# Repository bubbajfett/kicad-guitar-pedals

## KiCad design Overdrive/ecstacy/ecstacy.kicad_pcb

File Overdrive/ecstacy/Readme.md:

# Ecstacy

This is a clone of the Wampler ecstacy  overdrive.  

So this pedal is verified. I have not boxed this one yet, either.

All trademarks belong to their respective owners.

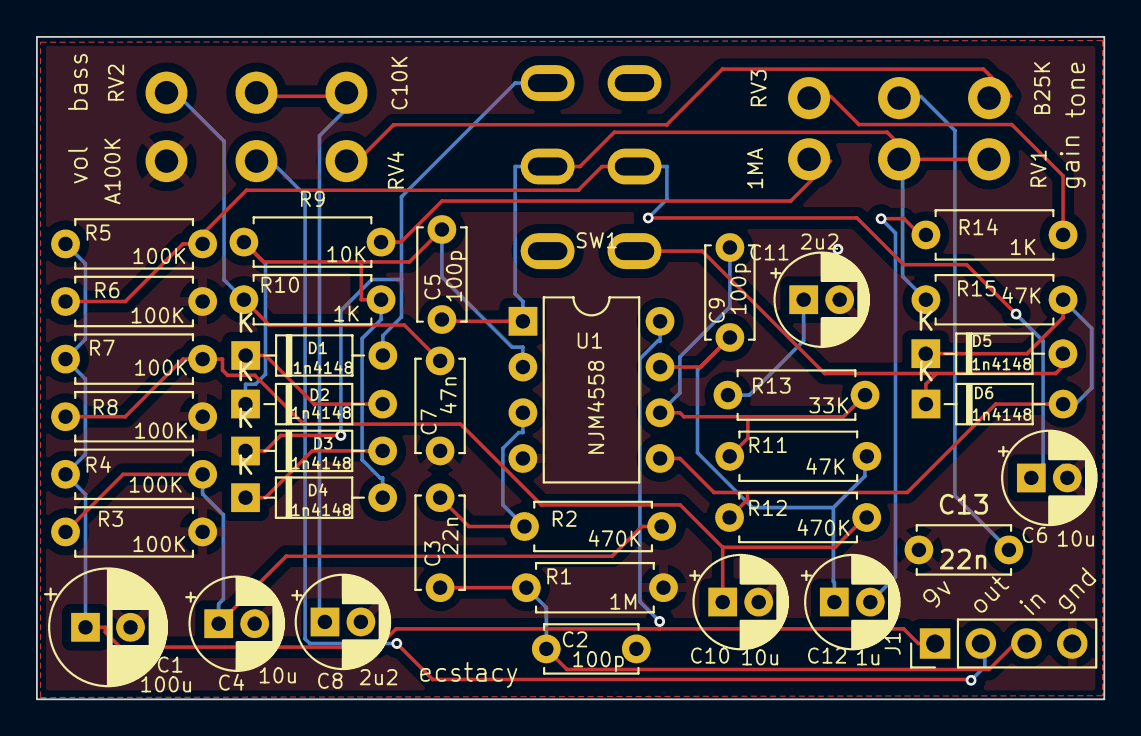
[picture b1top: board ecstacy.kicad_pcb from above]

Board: 2 copper layers, 59.3 x 36.8 mm, 41 parts (0 on the bottom side), 25 nets.

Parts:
C1: 100u; CP_Radial_D6.3mm_P2.50mm
C2, C5, C9: 100p; C_Disc_D5.0mm_W2.5mm_P5.00mm
C3, C13: 22n; C_Disc_D5.0mm_W2.5mm_P5.00mm
C4, C6, C10: 10u; CP_Radial_D5.0mm_P2.00mm
C7: 47n; C_Disc_D5.0mm_W2.5mm_P5.00mm
C8, C11: 2u2; CP_Radial_D5.0mm_P2.00mm
C12: 1u; CP_Radial_D5.0mm_P2.00mm
D1, D2, D3, D4, D5, D6: 1n4148; D_DO-35_SOD27_P7.62mm_Horizontal
J1: Conn_01x04_Pin; PinHeader_1x04_P2.54mm_Vertical
R1: 1M; R_Axial_DIN0207_L6.3mm_D2.5mm_P7.62mm_Horizontal
R2, R12: 470K; R_Axial_DIN0207_L6.3mm_D2.5mm_P7.62mm_Horizontal
R3, R4, R5, R6, R7, R8: 100K; R_Axial_DIN0207_L6.3mm_D2.5mm_P7.62mm_Horizontal
R9: 10K; R_Axial_DIN0207_L6.3mm_D2.5mm_P7.62mm_Horizontal
R10, R14: 1K; R_Axial_DIN0207_L6.3mm_D2.5mm_P7.62mm_Horizontal
R11, R15: 47K; R_Axial_DIN0207_L6.3mm_D2.5mm_P7.62mm_Horizontal
R13: 33K; R_Axial_DIN0207_L6.3mm_D2.5mm_P7.62mm_Horizontal
RV1: 1MA; Pot_Underside
RV2: C10K; Pot_Underside
RV3: B25K; Pot_Underside
RV4: A100K; Pot_Underside
SW1: SW_DPDT_x2; SWITCH-M1-DPDT
U1: NJM4558; DIP-8_W7.62mm

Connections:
9v: C1.1, J1.1, R4.1, R5.1, R7.1, U1.8 (V+)
GND: C1.2, C2.2, C4.2, C6.2, C7.1, C8.2, C10.2, C11.2, C13.1, J1.4, R1.2, R3.2, R6.2, R8.2, RV4.1, U1.4 (V-)
unnamed: C7.2, R10.1, RV2.3
unnamed: C8.1, RV2.1, RV2.2
unnamed: C11.1, R13.1
unnamed: C9.1, C12.1, R11.2, U1.7
unnamed: C12.2, R14.1
unnamed: C13.2, RV3.2
unnamed: D1.2 (A), D3.1 (K), SW1.1 (A)
unnamed: D1.1 (K), D2.2 (A)
unnamed: C5.2, D2.1 (K), D4.2 (A), R9.1, R10.2, U1.2 (-)
unnamed: D3.2 (A), D4.1 (K)
unnamed: D5.2 (A), D6.1 (K), SW1.6 (C)
unnamed: D5.1 (K), D6.2 (A), R12.1, R15.2, U1.5 (+)
unnamed: R9.2, RV1.1
unnamed: R14.2, RV3.3
unnamed: RV3.1, RV4.3
unnamed: C5.1, R15.1, RV1.2, RV1.3, SW1.2 (B), U1.1
unnamed: C3.2, R2.1, U1.3 (+)
unnamed: C9.2, R11.1, R13.2, U1.6 (-)
VB1: C4.1, R2.2, R3.1, R4.2
VB2: C6.1, R5.2, R6.1, SW1.5 (B)
VB3: C10.1, R7.2, R8.1, R12.2
in: C2.1, C3.1, J1.3, R1.1
out: J1.2, RV4.2

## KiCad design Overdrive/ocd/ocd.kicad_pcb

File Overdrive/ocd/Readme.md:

# ocd

This is a clone of the Fulltone OCD overdrive.

This pedal is verified. I have not boxed this one yet.

All trademarks belong to their respective owners.

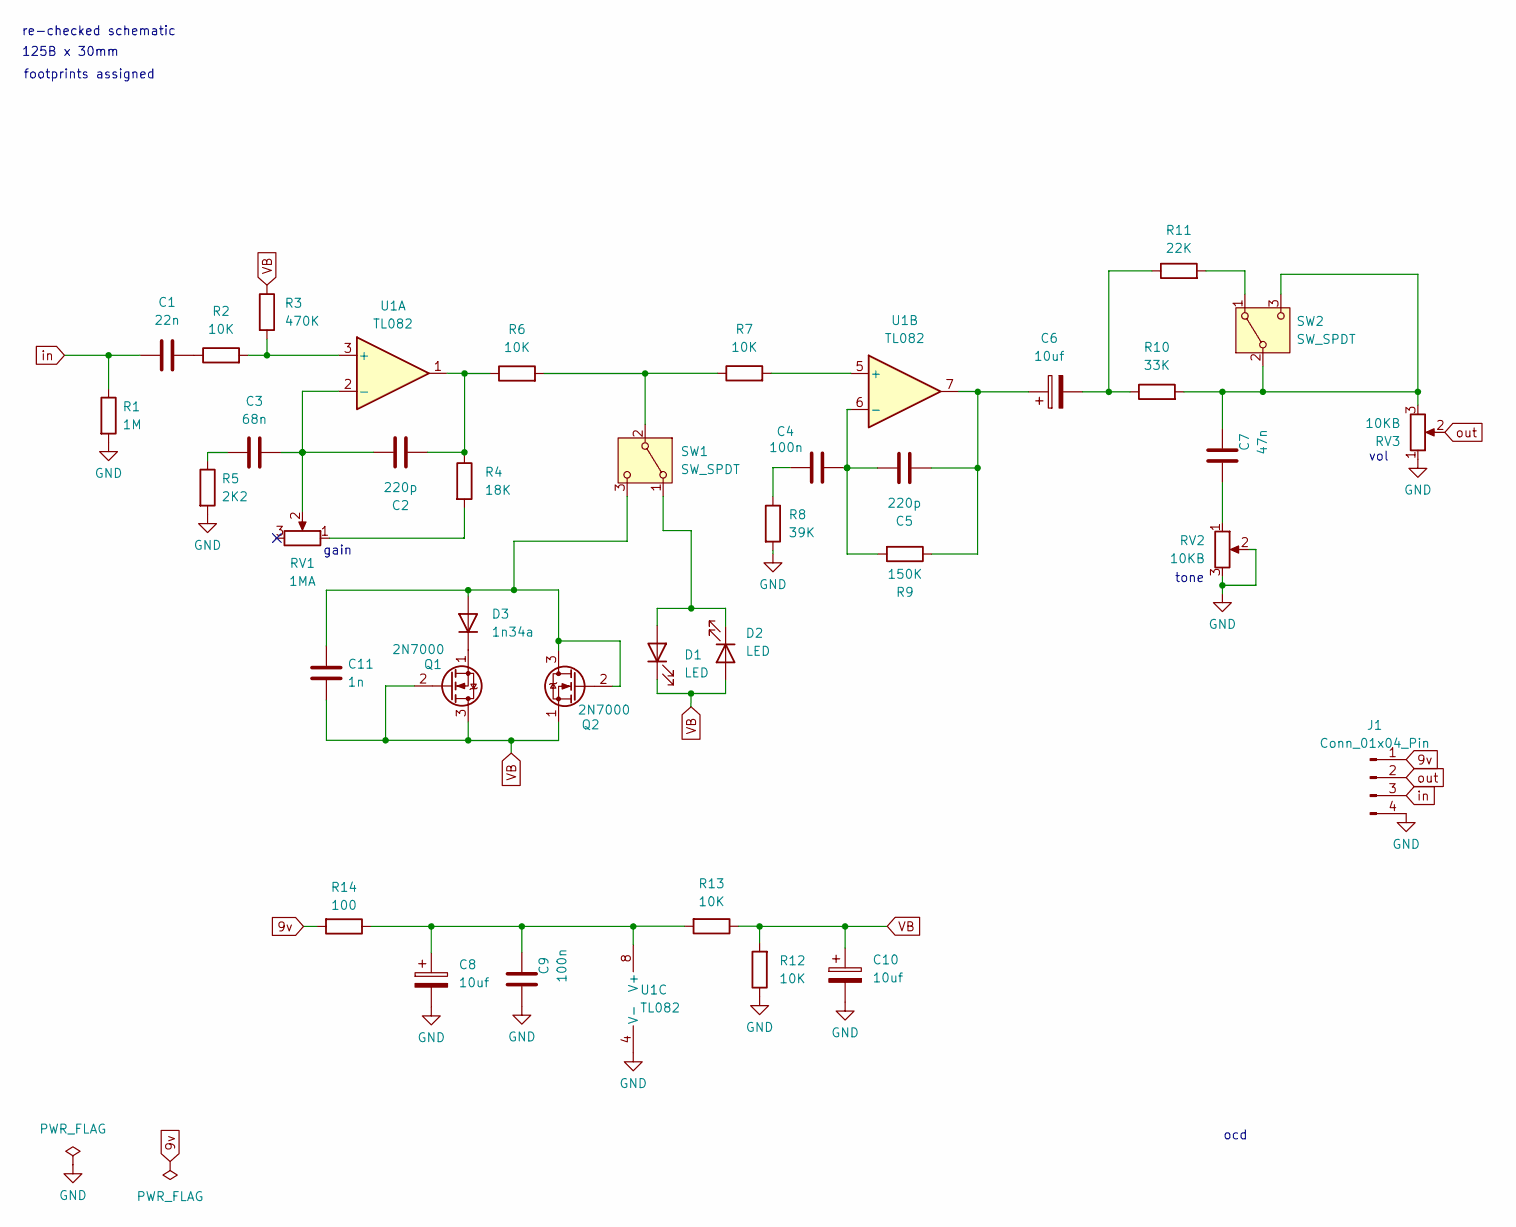
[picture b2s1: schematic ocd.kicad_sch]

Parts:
C1: 22n; C_Rect_L7.0mm_W2.0mm_P5.00mm
C2, C5: 220p; C_Rect_L7.0mm_W2.0mm_P5.00mm
C3: 68n; C_Rect_L7.0mm_W2.0mm_P5.00mm
C4, C9: 100n; C_Rect_L7.0mm_W2.0mm_P5.00mm
C6, C8, C10: 10uf; CP_Radial_D5.0mm_P2.00mm
C7: 47n; C_Rect_L7.0mm_W2.0mm_P5.00mm
C11: 1n; C_Rect_L7.0mm_W2.0mm_P5.00mm
D1, D2: LED; LED_D3.0mm
D3: 1n34a; D_DO-34_SOD68_P7.62mm_Horizontal
J1: Conn_01x04_Pin; PinHeader_1x04_P2.54mm_Vertical
Q1, Q2: 2N7000; TO-92_Inline
R1: 1M; R_Axial_DIN0207_L6.3mm_D2.5mm_P7.62mm_Horizontal
R2, R6, R7, R12, R13: 10K; R_Axial_DIN0207_L6.3mm_D2.5mm_P7.62mm_Horizontal
R3: 470K; R_Axial_DIN0207_L6.3mm_D2.5mm_P7.62mm_Horizontal
R4: 18K; R_Axial_DIN0207_L6.3mm_D2.5mm_P7.62mm_Horizontal
R5: 2K2; R_Axial_DIN0207_L6.3mm_D2.5mm_P7.62mm_Horizontal
R8: 39K; R_Axial_DIN0207_L6.3mm_D2.5mm_P7.62mm_Horizontal
R9: 150K; R_Axial_DIN0207_L6.3mm_D2.5mm_P7.62mm_Horizontal
R10: 33K; R_Axial_DIN0207_L6.3mm_D2.5mm_P7.62mm_Horizontal
R11: 22K; R_Axial_DIN0207_L6.3mm_D2.5mm_P7.62mm_Horizontal
R14: 100; R_Axial_DIN0207_L6.3mm_D2.5mm_P7.62mm_Horizontal
RV1: 1MA; Pot_Underside
RV2, RV3: 10KB; Pot_Underside
SW1, SW2: SW_SPDT; SWITCH-M1-SPDT
U1: TL082; DIP-8_W7.62mm

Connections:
9v: J1.1, R14.2
GND: C8.2, C9.1, C10.2, J1.4, R1.2, R5.2, R8.2, R12.1, RV2.2, RV2.3, RV3.1, U1.4 (V-)
unnamed: C1.2, R2.1
unnamed: C2.1, R4.1, R6.1, U1.1
unnamed: C3.1, R5.1
unnamed: C4.1, R8.1
unnamed: C5.1, C6.1, R9.1, U1.7
unnamed: C6.2, R10.1, R11.1
unnamed: C7.1, RV2.1
unnamed: D1.2 (A), D2.1 (K), SW1.1 (A)
unnamed: C11.2, D3.2 (A), Q2.2 (G), Q2.3 (D), SW1.3 (C)
unnamed: D3.1 (K), Q1.1 (S)
unnamed: R4.2, RV1.1
unnamed: R6.2, R7.1, SW1.2 (B)
unnamed: R11.2, SW2.1 (A)
unnamed: C7.2, R10.2, RV3.3, SW2.2 (B), SW2.3 (C)
unnamed: R2.2, R3.2, U1.3 (+)
unnamed: C2.2, C3.2, RV1.2, U1.2 (-)
unnamed: R7.2, U1.5 (+)
unnamed: C4.2, C5.2, R9.2, U1.6 (-)
unnamed: C8.1, C9.2, R13.2, R14.1, U1.8 (V+)
VB: C10.1, C11.1, D1.1 (K), D2.2 (A), Q1.2 (G), Q1.3 (D), Q2.1 (S), R3.1, R12.2, R13.1
in: C1.1, J1.3, R1.1
out: J1.2, RV3.2

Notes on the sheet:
footprints assigned
vol
tone
125B x 30mm
gain
re-checked schematic
ocd

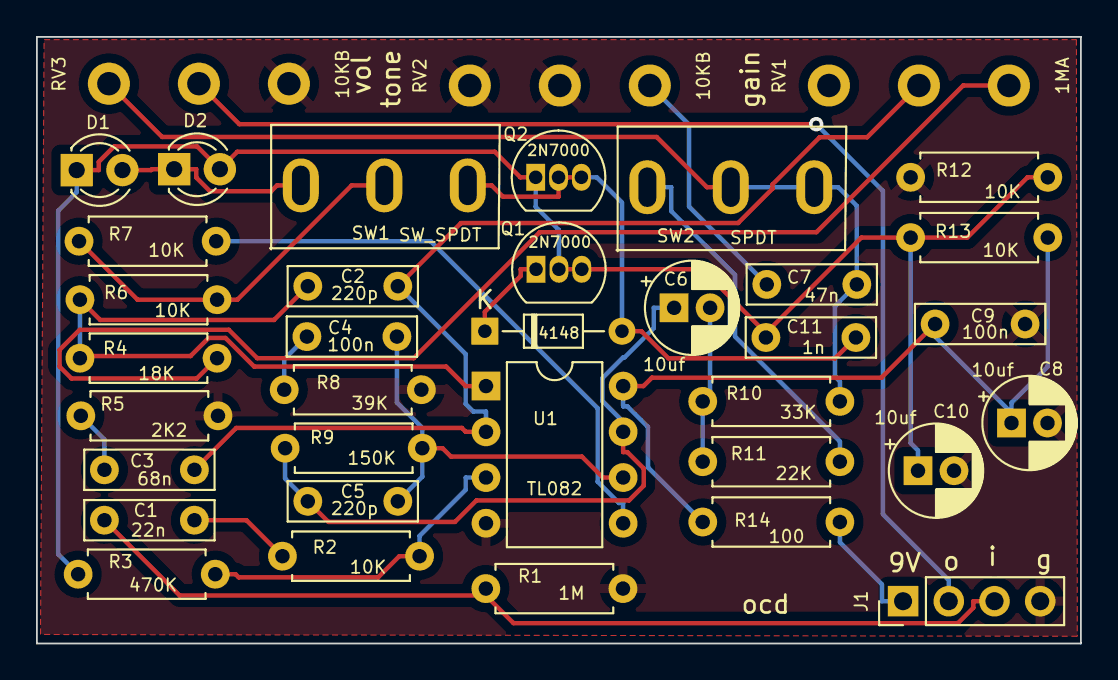
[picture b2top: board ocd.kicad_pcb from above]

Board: 2 copper layers, 58.0 x 33.7 mm, 37 parts (0 on the bottom side), 24 nets.

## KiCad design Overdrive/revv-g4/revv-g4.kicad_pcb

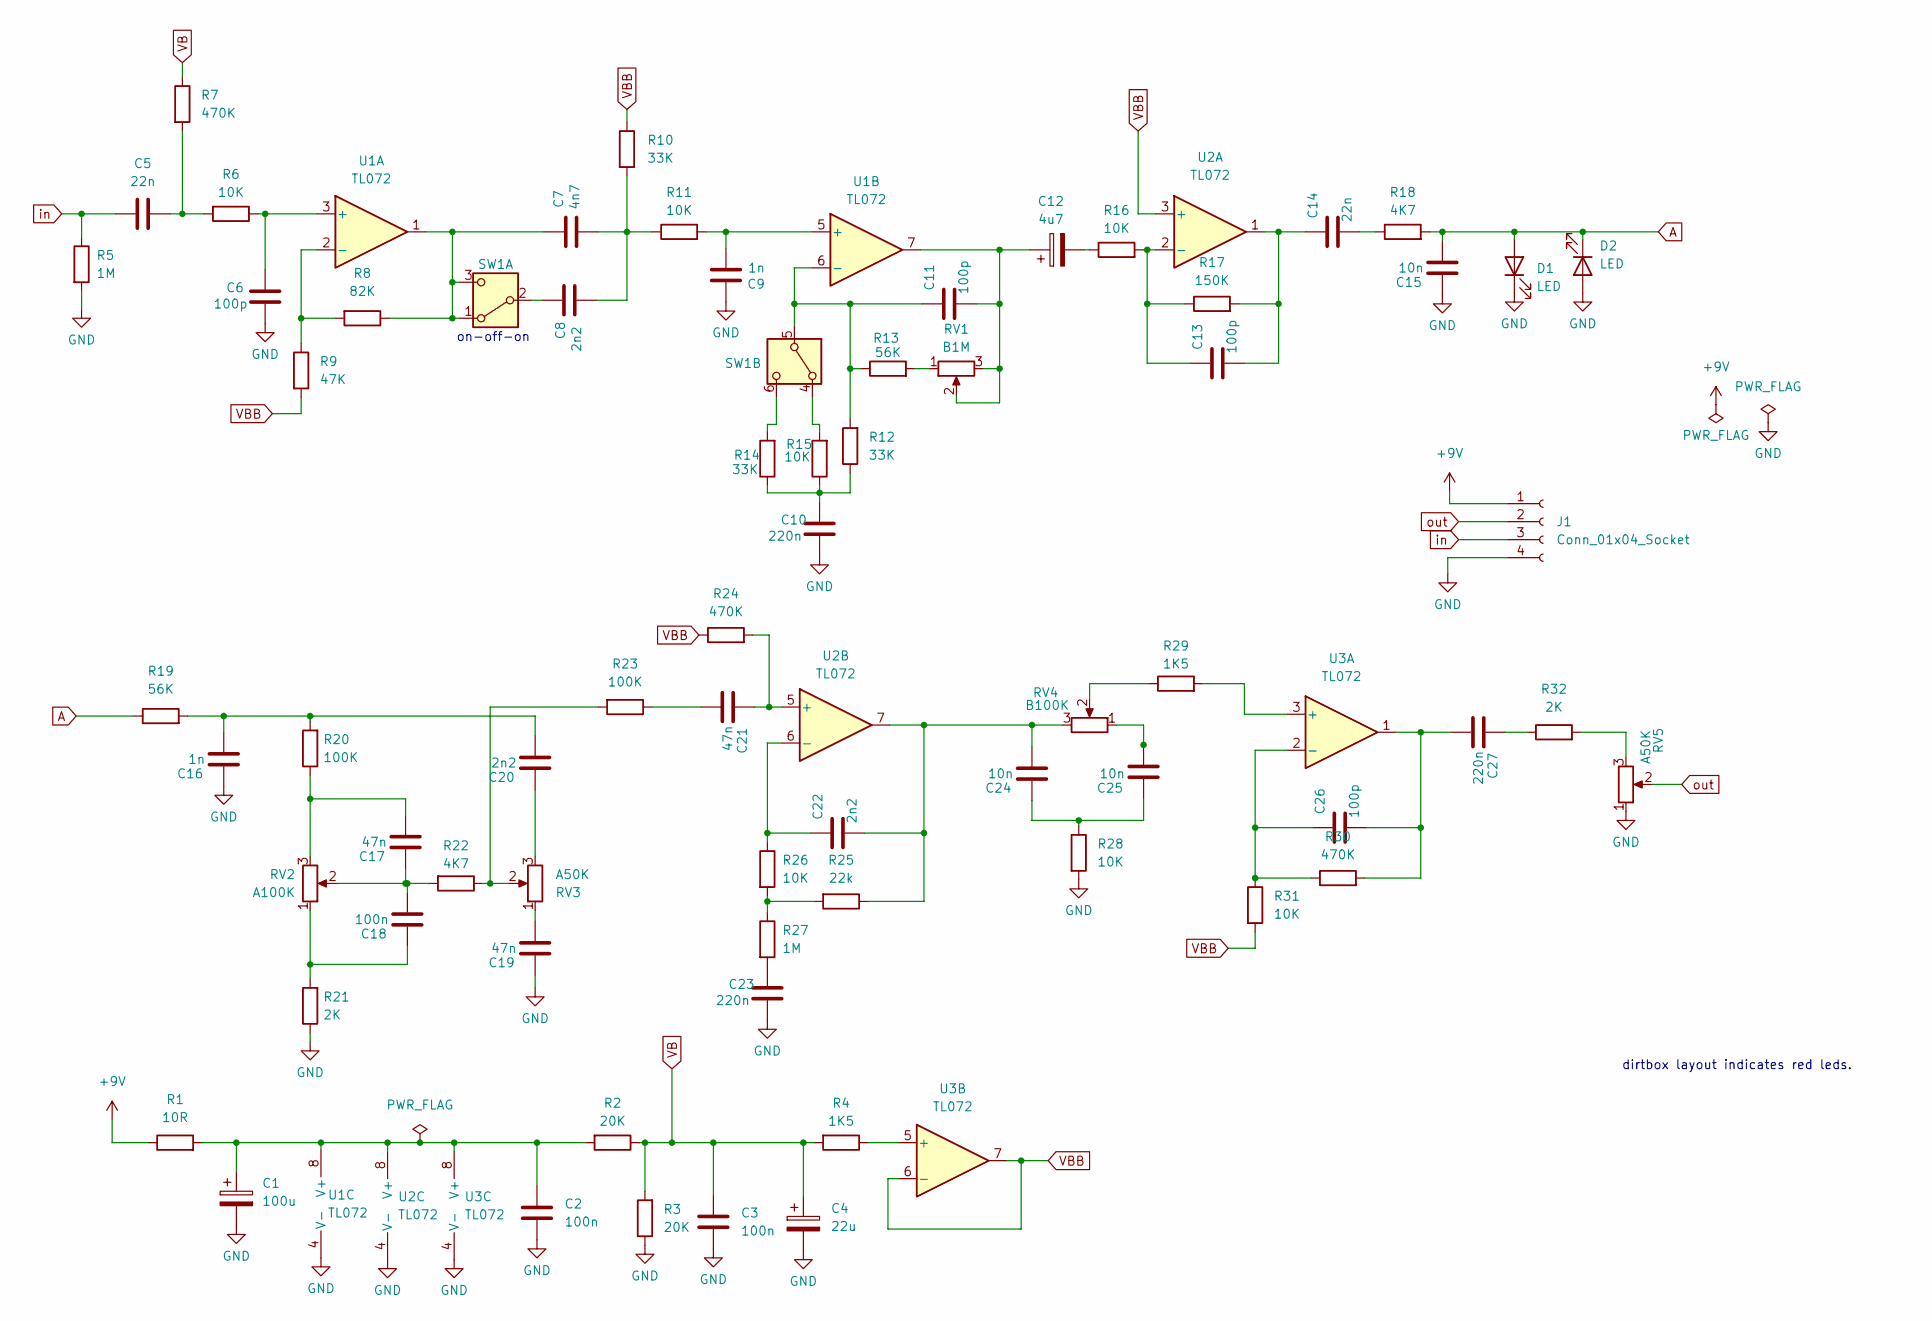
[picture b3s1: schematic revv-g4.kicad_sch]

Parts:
C1: 100u; CP_Radial_D6.3mm_P2.50mm
C2, C3, C18: 100n; C_Rect_L7.0mm_W3.5mm_P5.00mm
C4: 22u; CP_Radial_D5.0mm_P2.00mm
C5, C14: 22n; C_Rect_L7.0mm_W3.5mm_P5.00mm
C6, C11, C13, C26: 100p; C_Disc_D4.7mm_W2.5mm_P5.00mm
C7: 4n7; C_Rect_L7.0mm_W3.5mm_P5.00mm
C8, C20, C22: 2n2; C_Rect_L7.0mm_W3.5mm_P5.00mm
C9, C16: 1n; C_Rect_L7.0mm_W3.5mm_P5.00mm
C10, C23, C27: 220n; C_Rect_L7.0mm_W3.5mm_P5.00mm
C12: 4u7; CP_Radial_D5.0mm_P2.00mm
C15, C24, C25: 10n; C_Rect_L7.0mm_W3.5mm_P5.00mm
C17, C19, C21: 47n; C_Rect_L7.0mm_W3.5mm_P5.00mm
D1, D2: LED; LED_D3.0mm
J1: Conn_01x04_Socket; PinHeader_1x04_P2.54mm_Vertical
R1: 10R; R_Axial_DIN0207_L6.3mm_D2.5mm_P7.62mm_Horizontal
R2, R3: 20K; R_Axial_DIN0207_L6.3mm_D2.5mm_P7.62mm_Horizontal
R4, R29: 1K5; R_Axial_DIN0207_L6.3mm_D2.5mm_P7.62mm_Horizontal
R5, R27: 1M; R_Axial_DIN0207_L6.3mm_D2.5mm_P7.62mm_Horizontal
R6, R11, R15, R16, R26, R28, R31: 10K; R_Axial_DIN0207_L6.3mm_D2.5mm_P7.62mm_Horizontal
R7, R24, R30: 470K; R_Axial_DIN0207_L6.3mm_D2.5mm_P7.62mm_Horizontal
R8: 82K; R_Axial_DIN0207_L6.3mm_D2.5mm_P7.62mm_Horizontal
R9: 47K; R_Axial_DIN0207_L6.3mm_D2.5mm_P7.62mm_Horizontal
R10, R12, R14: 33K; R_Axial_DIN0207_L6.3mm_D2.5mm_P7.62mm_Horizontal
R13, R19: 56K; R_Axial_DIN0207_L6.3mm_D2.5mm_P7.62mm_Horizontal
R17: 150K; R_Axial_DIN0207_L6.3mm_D2.5mm_P7.62mm_Horizontal
R18, R22: 4K7; R_Axial_DIN0207_L6.3mm_D2.5mm_P7.62mm_Horizontal
R20, R23: 100K; R_Axial_DIN0207_L6.3mm_D2.5mm_P7.62mm_Horizontal
R21, R32: 2K; R_Axial_DIN0207_L6.3mm_D2.5mm_P7.62mm_Horizontal
R25: 22k; R_Axial_DIN0207_L6.3mm_D2.5mm_P7.62mm_Horizontal
RV1: B1M; Pot_Underside
RV2: A100K; Pot_Underside
RV3, RV5: A50K; Pot_Underside
RV4: B100K; Pot_Underside
SW1: SW_DPDT_x2; SWITCH-M1-DPDT
U1, U2, U3: TL072; DIP-8_W7.62mm

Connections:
+9V: J1.1, R1.1
A: C15.1, D1.2 (A), D2.1 (K), R18.2, R19.1
GND: C1.2, C2.2, C3.2, C4.2, C6.1, C9.2, C10.1, C15.2, C16.2, C19.2, C23.1, D1.1 (K), D2.2 (A), J1.4, R3.1, R5.2, R21.1, R28.2, RV5.1, U1.4 (V-), U2.4 (V-), U3.4 (V-)
unnamed: C5.2, R6.2, R7.2
unnamed: C7.1, C8.1, R10.2, R11.1
unnamed: C10.2, R12.1, R14.1, R15.1
unnamed: C11.1, C12.1, RV1.2, RV1.3, U1.7
unnamed: C12.2, R16.1
unnamed: C13.1, C14.2, R17.2, U2.1
unnamed: C14.1, R18.1
unnamed: C16.1, C20.1, R19.2, R20.2
unnamed: C17.1, R20.1, RV2.3
unnamed: C17.2, C18.1, R22.2, RV2.2
unnamed: C18.2, R21.2, RV2.1
unnamed: C19.1, RV3.1
unnamed: C20.2, RV3.3
unnamed: C21.1, R23.1
unnamed: C22.1, C24.1, R25.1, RV4.3, U2.7
unnamed: C23.2, R27.2
unnamed: C24.2, C25.2, R28.1
unnamed: C25.1, RV4.1
unnamed: C26.1, C27.1, R30.2, U3.1
unnamed: C27.2, R32.1
unnamed: R13.2, RV1.1
unnamed: R22.1, R23.2, RV3.2
unnamed: R25.2, R26.2, R27.1
unnamed: R29.1, RV4.2
unnamed: R32.2, RV5.3
unnamed: C7.2, R8.1, SW1.1 (A), SW1.3 (C), U1.1
unnamed: C8.2, SW1.2 (B)
unnamed: R15.2, SW1.4 (A)
unnamed: C11.2, R12.2, R13.1, SW1.5 (B), U1.6 (-)
unnamed: R14.2, SW1.6 (C)
unnamed: C6.2, R6.1, U1.3 (+)
unnamed: R8.2, R9.1, U1.2 (-)
unnamed: C9.1, R11.2, U1.5 (+)
unnamed: C1.1, C2.1, R1.2, R2.2, U1.8 (V+), U2.8 (V+), U3.8 (V+)
unnamed: C13.2, R16.2, R17.1, U2.2 (-)
unnamed: C21.2, R24.2, U2.5 (+)
unnamed: C22.2, R26.1, U2.6 (-)
unnamed: R29.2, U3.3 (+)
unnamed: C26.2, R30.1, R31.1, U3.2 (-)
unnamed: R4.1, U3.5 (+)
VB: C3.1, C4.1, R2.1, R3.2, R4.2, R7.1
VBB: R9.2, R10.1, R24.1, R31.2, U2.3 (+), U3.6 (-), U3.7
in: C5.1, J1.3, R5.1
out: J1.2, RV5.2

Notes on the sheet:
dirtbox layout indicates red leds.
on-off-on

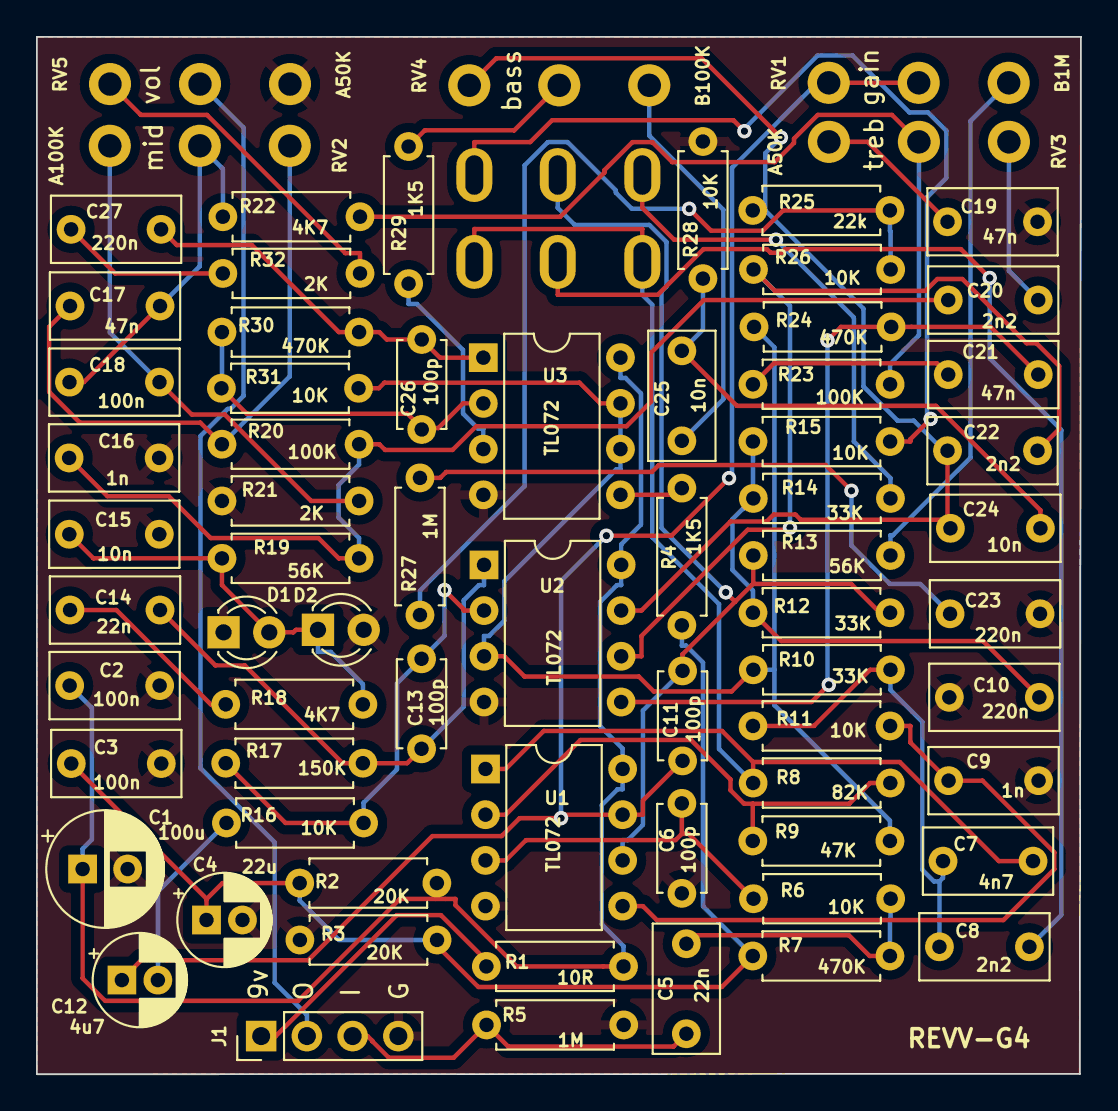
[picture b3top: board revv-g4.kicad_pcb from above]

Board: 2 copper layers, 58.0 x 57.6 mm, 71 parts (0 on the bottom side), 47 nets.

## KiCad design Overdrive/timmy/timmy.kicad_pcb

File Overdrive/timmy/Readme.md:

# Timmy clone

This is a clone of the Paul Cochrane Timmy overdrive.

This pedal is verified, though the layout is poor, IMHO.

It is the first pedal I did in Kicad, and it took 4 revisions
to get a working pedal, going all the way back to 2022.   This was
in the hall of shame box for some time.

v1:  pads for switch too small.   Changed to 2.5mm hole

v2:  RV2 is backwards from the tagboardeffects layout.   I.e.
the schematic has multiple issues.

Pedal has low volume.   Managed to get this to work correctly
via a series of bodges.  Also note te 3.3K resistor R2 is
diff in tagboardeffects layout 

v3:  Seems to work correctly.    Missing some values on
the silkscreen layer.

v4:  final version.      

All trademarks belong to their respective owners.

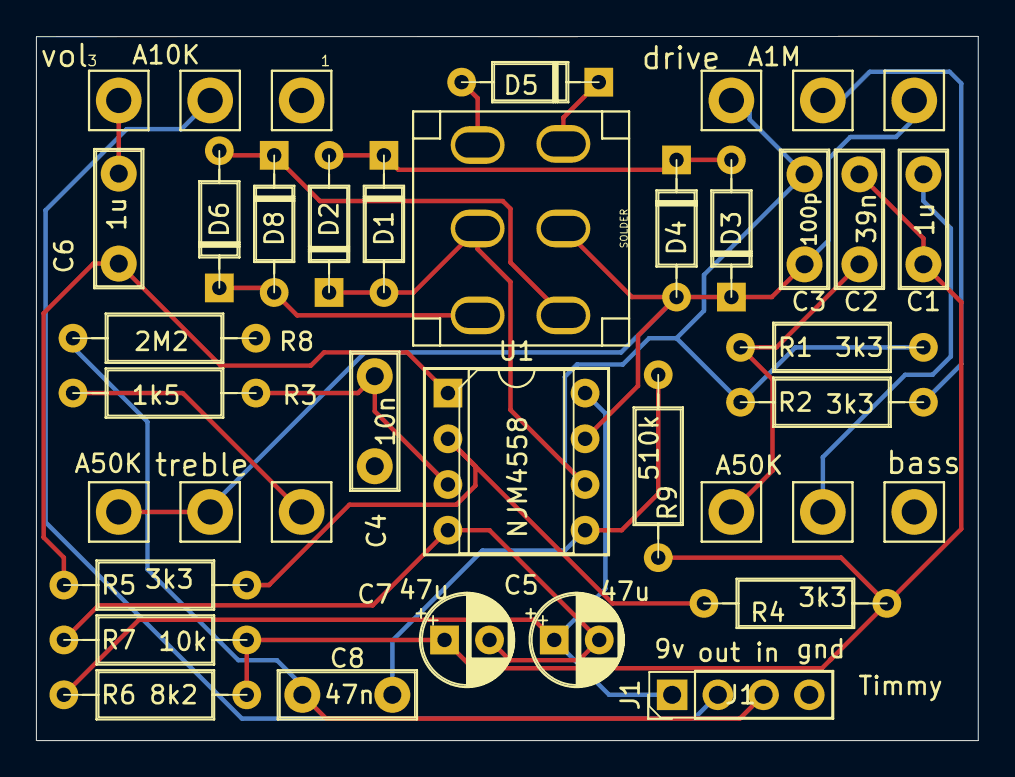
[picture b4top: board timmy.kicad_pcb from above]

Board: 2 copper layers, 52.3 x 39.1 mm, 31 parts (0 on the bottom side), 21 nets.

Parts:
C1, C6: 1u; C_Disc_D7.5mm_W2.5mm_P5.00mm
C2: 39n; C_Disc_D7.5mm_W2.5mm_P5.00mm
C3: 100p; C_Disc_D7.5mm_W2.5mm_P5.00mm
C4: 10n; C_Disc_D7.5mm_W2.5mm_P5.00mm
C5, C7: 47u; CP_Radial_D5.0mm_P2.50mm
C8: 47n; C_Disc_D7.5mm_W2.5mm_P5.00mm
D1, D2, D3, D4, D5, D6, D8: 1N4148; D_DO-35_SOD27_P7.62mm_Horizontal
J1: Conn_01x04_Female; PinHeader_1x04_P2.54mm_Vertical
R1, R2, R4, R5: 3k3; R_Axial_DIN0207_L6.3mm_D2.5mm_P10.16mm_Horizontal
R3: 1k5; R_Axial_DIN0207_L6.3mm_D2.5mm_P10.16mm_Horizontal
R6: 8k2; R_Axial_DIN0207_L6.3mm_D2.5mm_P10.16mm_Horizontal
R7: 10k; R_Axial_DIN0207_L6.3mm_D2.5mm_P10.16mm_Horizontal
R8: 2M2; R_Axial_DIN0207_L6.3mm_D2.5mm_P10.16mm_Horizontal
R9: 510k; R_Axial_DIN0207_L6.3mm_D2.5mm_P10.16mm_Horizontal
SW1: SW_DPDT_x2; DPDT.MINI3
U1: NJM4558; DIP-8_W7.62mm_Socket
bass: 50k; 16MM_PCB_PADS
drive: 1M; 16MM_PCB_PADS
treble: 50k; 16MM_PCB_PADS
vol: 10k; 16MM_PCB_PADS

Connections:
+9V: C5.1, J1.1, R6.1, U1.8 (V+)
GND: C4.1, C5.2, C7.2, J1.4, R7.2, R8.1, U1.4 (V-), vol.1
IN: C8.1, J1.3, R8.2
unnamed: C1.2, bass.2
unnamed: C2.2, R1.1, bass.3
unnamed: C3.1, D3.1 (K), D4.2 (A), SW1.5 (B), U1.7, drive.1, treble.2, treble.3
unnamed: C3.2, D1.2 (A), D2.1 (K), R1.2, R2.1, SW1.2 (B), U1.6 (-), drive.3
unnamed: C4.2, R3.2, U1.3 (+)
unnamed: C6.1, vol.3
unnamed: C6.2, R5.2, U1.1
unnamed: C8.2, R9.1, U1.5 (+)
unnamed: D1.1 (K), D2.2 (A), D3.2 (A), D4.1 (K)
unnamed: D5.1 (K), SW1.4 (A)
unnamed: D5.2 (A), SW1.1 (A)
unnamed: D6.1 (K), D8.2 (A), SW1.3 (C)
unnamed: D6.2 (A), D8.1 (K), SW1.6 (C)
unnamed: R2.2, drive.2
unnamed: R3.1, treble.1
unnamed: R4.2, R5.1, U1.2 (-)
OUT: J1.2, vol.2
VB: C1.1, C2.1, C7.1, R4.1, R6.2, R7.1, R9.2

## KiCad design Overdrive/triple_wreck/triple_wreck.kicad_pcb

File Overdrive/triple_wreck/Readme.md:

# triple wreck

This is a clone of the Wampler triple wreck overdrive.  Very nice
overdrive.   Very nice sound.

This is the 2nd version of the pedal.   The first version was 3mm too wide
to fit into a 125B.

So this pedal circuit  is verified. I have not boxed this one yet, either.

All trademarks belong to their respective owners.

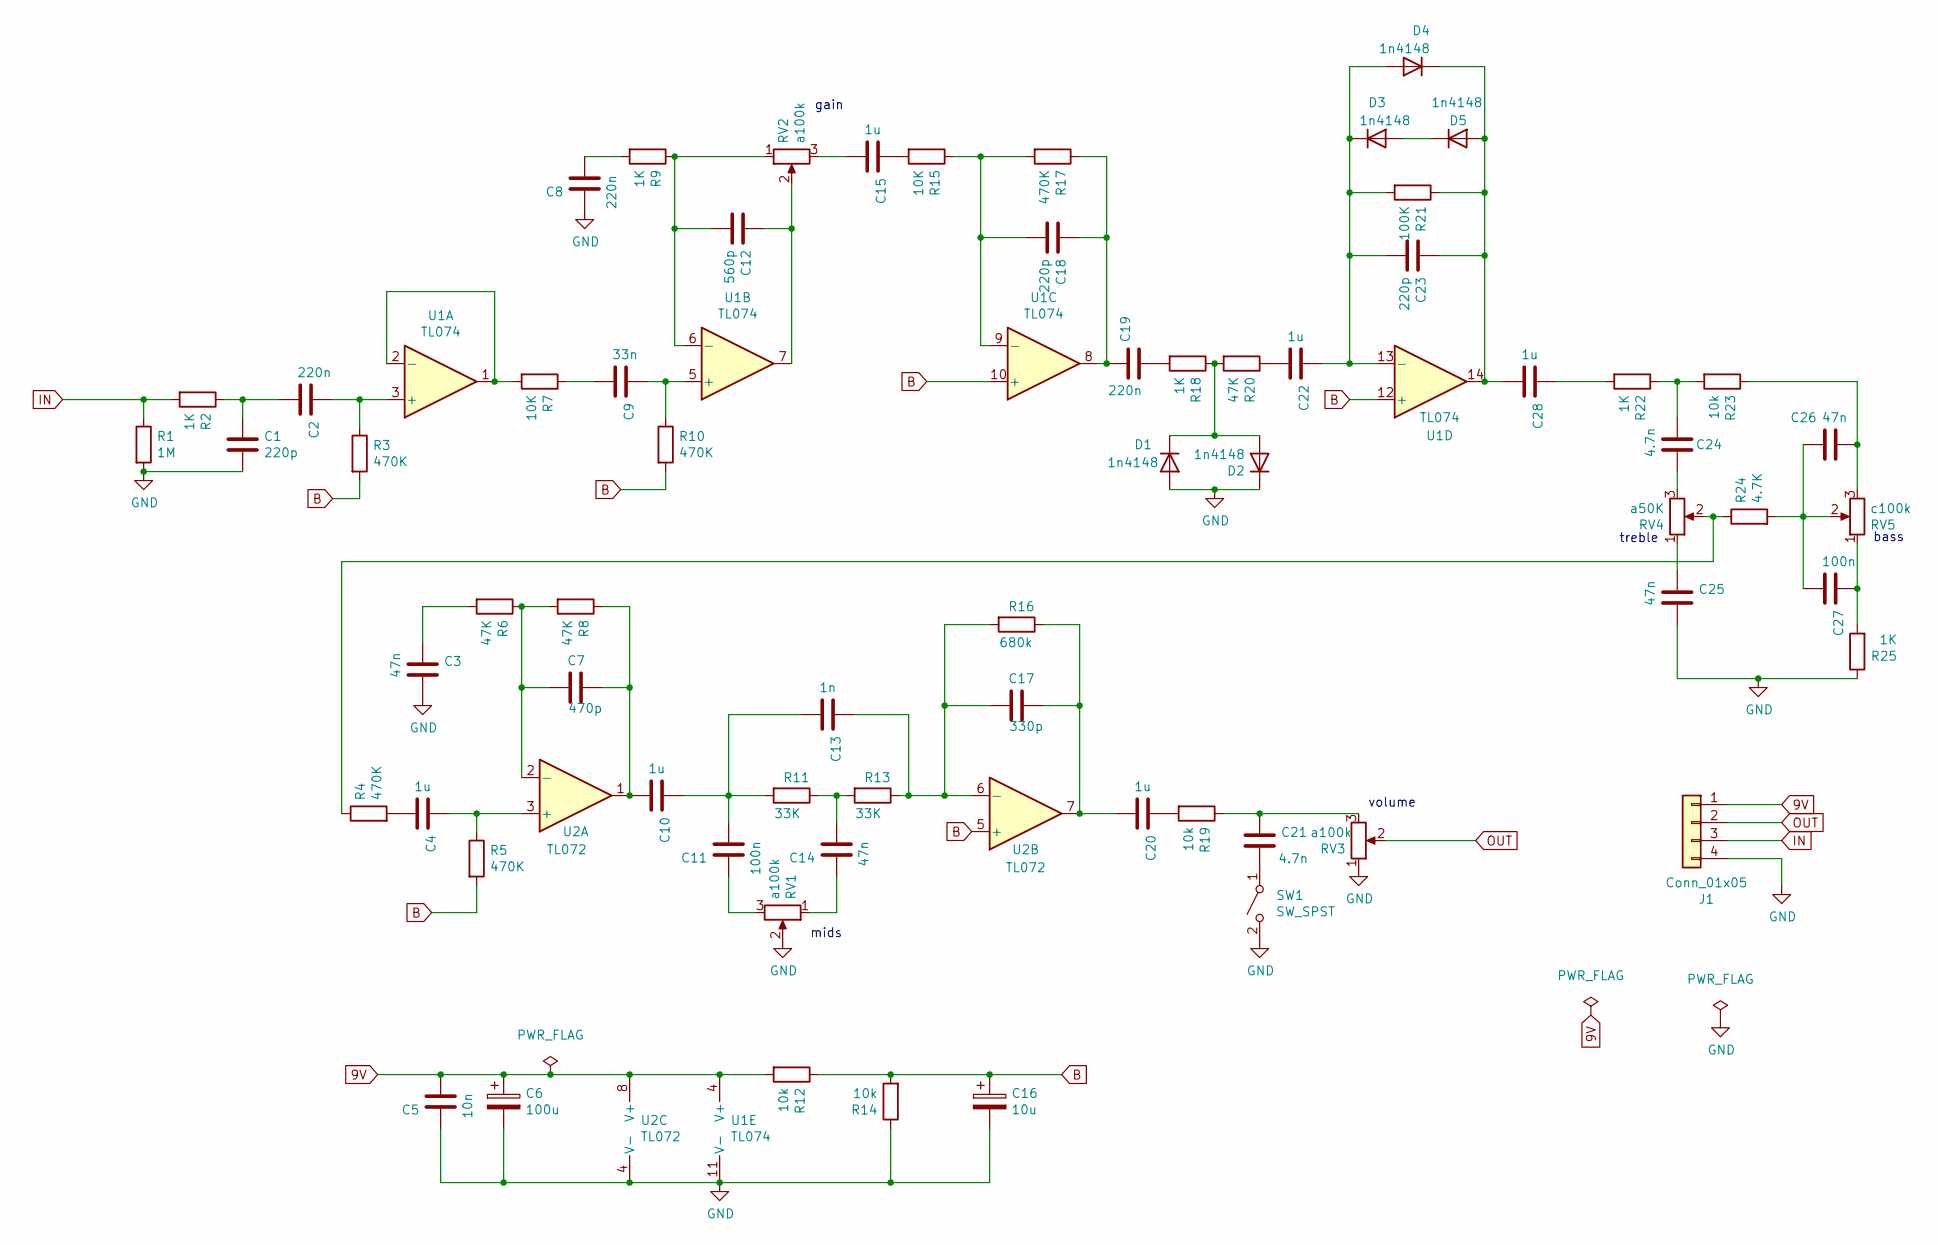
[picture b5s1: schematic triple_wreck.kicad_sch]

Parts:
C1, C18: 220p; C_Disc_D3.8mm_W2.6mm_P2.50mm
C2, C8, C19: 220n; C_Rect_L7.0mm_W3.5mm_P5.00mm
C3, C14, C25, C26: 47n; C_Rect_L7.0mm_W3.5mm_P5.00mm
C4, C10, C15, C20, C22, C28: 1u; C_Rect_L7.0mm_W3.5mm_P5.00mm
C5: 10n; C_Rect_L7.0mm_W3.5mm_P5.00mm
C6: 100u; CP_Radial_D8.0mm_P2.50mm
C7: 470p; C_Disc_D3.8mm_W2.6mm_P2.50mm
C9: 33n; C_Rect_L7.0mm_W3.5mm_P5.00mm
C11, C27: 100n; C_Rect_L7.0mm_W3.5mm_P5.00mm
C12: 560p; C_Disc_D3.8mm_W2.6mm_P2.50mm
C13: 1n; C_Rect_L7.0mm_W3.5mm_P5.00mm
C16: 10u; CP_Radial_D6.3mm_P2.50mm
C17: 330p; C_Disc_D3.8mm_W2.6mm_P2.50mm
C21, C24: 4.7n; C_Rect_L7.0mm_W3.5mm_P5.00mm
C23: 220p; C_Disc_D5.1mm_W3.2mm_P5.00mm
D1, D2, D3, D4, D5: 1n4148; D_A-405_P7.62mm_Horizontal
J1: Conn_01x05; PinHeader_1x04_P2.54mm_Vertical
R1: 1M; R_Axial_DIN0207_L6.3mm_D2.5mm_P10.16mm_Horizontal
R2, R9, R18, R22, R25: 1K; R_Axial_DIN0207_L6.3mm_D2.5mm_P10.16mm_Horizontal
R3, R4, R5, R10, R17: 470K; R_Axial_DIN0207_L6.3mm_D2.5mm_P10.16mm_Horizontal
R6, R8, R20: 47K; R_Axial_DIN0207_L6.3mm_D2.5mm_P10.16mm_Horizontal
R7, R15: 10K; R_Axial_DIN0207_L6.3mm_D2.5mm_P10.16mm_Horizontal
R11, R13: 33K; R_Axial_DIN0207_L6.3mm_D2.5mm_P10.16mm_Horizontal
R12, R14, R19, R23: 10k; R_Axial_DIN0207_L6.3mm_D2.5mm_P10.16mm_Horizontal
R16: 680k; R_Axial_DIN0207_L6.3mm_D2.5mm_P10.16mm_Horizontal
R21: 100K; R_Axial_DIN0207_L6.3mm_D2.5mm_P10.16mm_Horizontal
R24: 4.7K; R_Axial_DIN0207_L6.3mm_D2.5mm_P10.16mm_Horizontal
RV1, RV2, RV3: a100k; Pot_Underside
RV4: a50K; Pot_Underside
RV5: c100k; Pot_Underside
SW1: SW_SPST; SWITCH_SPDT_PTH_11.6X4.0MM_LOCK
U1: TL074; DIP-14_W7.62mm_Socket
U2: TL072; DIP-8_W7.62mm

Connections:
9V: C5.2, C6.1, J1.1, R12.2, U1.4 (V+), U2.8 (V+)
B: C16.1, R3.2, R5.2, R10.2, R12.1, R14.2, U1.10 (+), U1.12 (+), U2.5 (+)
GND: C1.2, C3.2, C5.1, C6.2, C8.1, C16.2, C25.2, D1.2 (A), D2.1 (K), J1.4, R1.2, R14.1, R25.1, RV1.2, RV3.1, SW1.2 (B), U1.11 (V-), U2.4 (V-)
IN: J1.3, R1.1, R2.2
unnamed: C1.1, C2.2, R2.1
unnamed: C3.1, R6.2
unnamed: C4.2, R4.2
unnamed: C8.2, R9.2
unnamed: C9.2, R7.1
unnamed: C10.1, C11.2, C13.2, R11.2
unnamed: C7.1, C10.2, R8.1, U2.1
unnamed: C11.1, RV1.3
unnamed: C12.1, RV2.2, U1.7
unnamed: C14.1, RV1.1
unnamed: C14.2, R11.1, R13.2
unnamed: C15.1, R15.2
unnamed: C15.2, RV2.3
unnamed: C17.1, C20.2, R16.1, U2.7
unnamed: C18.1, C19.1, R17.1, U1.8
unnamed: C19.2, R18.2
unnamed: C20.1, R19.2
unnamed: C21.1, R19.1, RV3.3
unnamed: C22.2, R20.1
unnamed: C24.1, R22.1, R23.2
unnamed: C24.2, RV4.3
unnamed: C25.1, RV4.1
unnamed: C26.1, R23.1, RV5.3
unnamed: C26.2, C27.2, R24.2, RV5.2
unnamed: C27.1, R25.2, RV5.1
unnamed: C28.1, R22.2
unnamed: D1.1 (K), D2.2 (A), R18.1, R20.2
unnamed: D3.2 (A), D5.1 (K)
unnamed: C22.1, C23.2, D3.1 (K), D4.2 (A), R21.2, U1.13 (-)
unnamed: C23.1, C28.2, D4.1 (K), D5.2 (A), R21.1, U1.14
unnamed: R4.1, R24.1, RV4.2
unnamed: C21.2, SW1.1 (A)
unnamed: C2.1, R3.1, U1.3 (+)
unnamed: R7.2, U1.1, U1.2 (-)
unnamed: C9.1, R10.1, U1.5 (+)
unnamed: C12.2, R9.1, RV2.1, U1.6 (-)
unnamed: C18.2, R15.1, R17.2, U1.9 (-)
unnamed: C4.1, R5.1, U2.3 (+)
unnamed: C7.2, R6.1, R8.2, U2.2 (-)
unnamed: C13.1, C17.2, R13.1, R16.2, U2.6 (-)
OUT: J1.2, RV3.2

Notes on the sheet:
mids
volume
treble
bass
gain

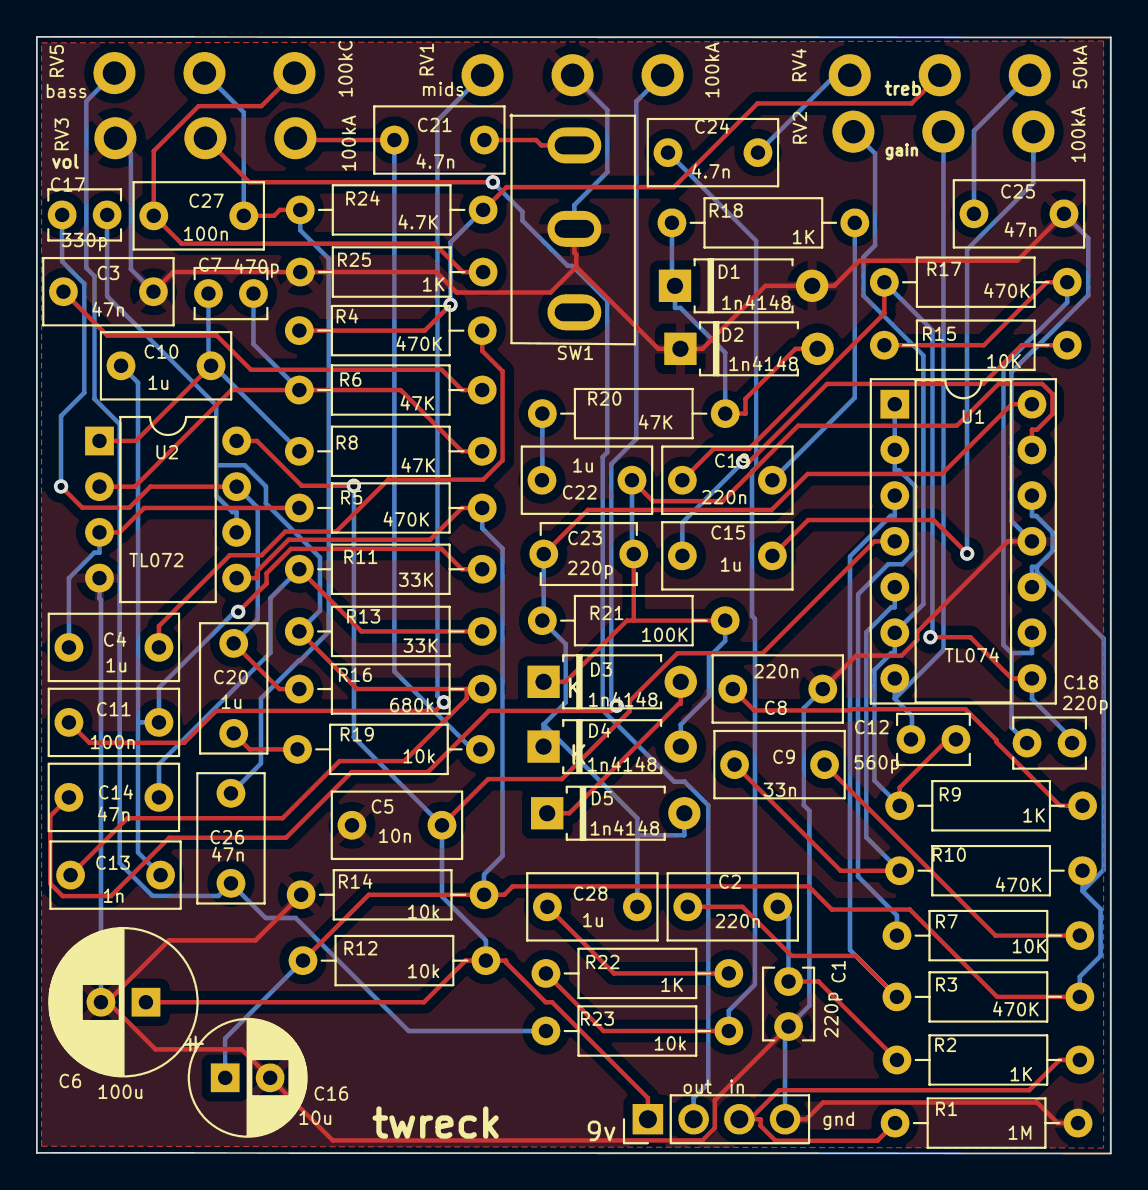
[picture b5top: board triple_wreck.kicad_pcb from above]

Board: 2 copper layers, 59.7 x 62.0 mm, 67 parts (0 on the bottom side), 45 nets.

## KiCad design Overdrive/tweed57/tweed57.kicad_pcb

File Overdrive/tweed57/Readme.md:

# tweed57

This is a clone of the Wampler tweed57 overdrive.

This pedal is verified. I have not boxed this one yet.
I want to re-do this one using SMD J201.

All trademarks belong to their respective owners.

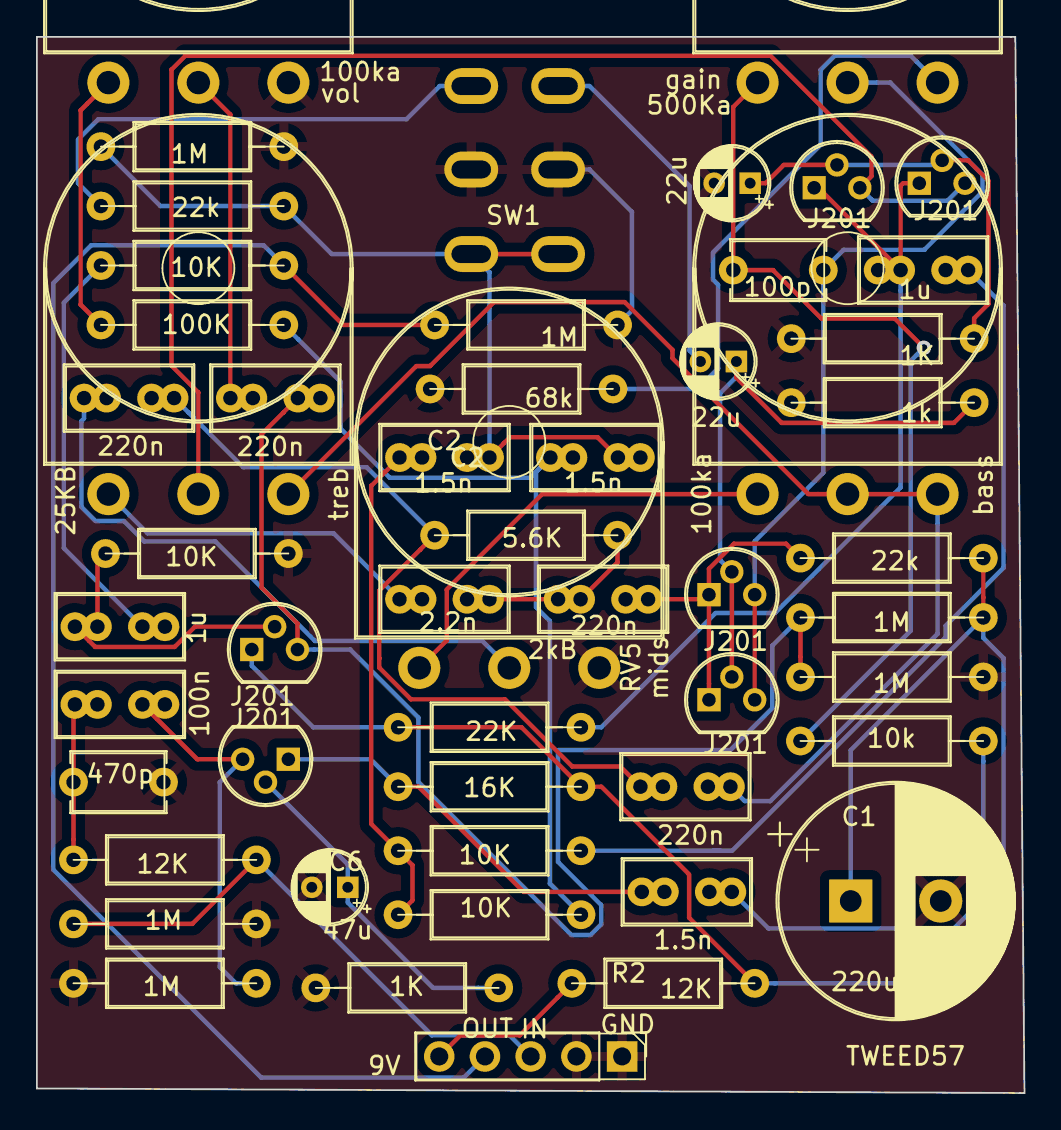
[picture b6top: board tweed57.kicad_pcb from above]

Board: 2 copper layers, 54.9 x 58.7 mm, 53 parts (0 on the bottom side), 35 nets.

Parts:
C1: 220u; CP_Radial_D13.0mm_P5.00mm
C2, C5, C7: 1.5n; C_Rect_L7.0mm_W3.5mm_P2.50mm_P5.00mm
C3: 470p; C_Disc_D5.1mm_W3.2mm_P5.00mm
C4: 100n; C_Rect_L7.0mm_W3.5mm_P2.50mm_P5.00mm
C6: 47u; CP_Radial_D4.0mm_P2.00mm
C8: 100p; C_Disc_D5.1mm_W3.2mm_P5.00mm
C9, C12, C14, C15: 220n; C_Rect_L7.0mm_W3.5mm_P2.50mm_P5.00mm
C10, C13: 1u; C_Rect_L7.0mm_W3.5mm_P2.50mm_P5.00mm
C11, C17: 22u; CP_Radial_D4.0mm_P2.00mm
C16: 2.2n; C_Rect_L7.0mm_W3.5mm_P2.50mm_P5.00mm
J1: Conn_01x05; PinHeader_1x05_P2.54mm_Vertical
Q1, Q2, Q3, Q4, Q5, Q6: J201; TO-92
R1, R5, R6, R13, R14, R20: 1M; R_Axial_DIN0207_L6.3mm_D2.5mm_P10.16mm_Horizontal
R2, R3: 12K; R_Axial_DIN0207_L6.3mm_D2.5mm_P10.16mm_Horizontal
R4, R12, R17, R19: 10K; R_Axial_DIN0207_L6.3mm_D2.5mm_P10.16mm_Horizontal
R7: 100K; R_Axial_DIN0207_L6.3mm_D2.5mm_P10.16mm_Horizontal
R8: 16K; R_Axial_DIN0207_L6.3mm_D2.5mm_P10.16mm_Horizontal
R9, R21: 1K; R_Axial_DIN0207_L6.3mm_D2.5mm_P10.16mm_Horizontal
R10: 10k; R_Axial_DIN0207_L6.3mm_D2.5mm_P10.16mm_Horizontal
R11: 68k; R_Axial_DIN0207_L6.3mm_D2.5mm_P10.16mm_Horizontal
R15: 1k; R_Axial_DIN0207_L6.3mm_D2.5mm_P10.16mm_Horizontal
R16, R23: 22k; R_Axial_DIN0207_L6.3mm_D2.5mm_P10.16mm_Horizontal
R18: 5.6K; R_Axial_DIN0207_L6.3mm_D2.5mm_P10.16mm_Horizontal
R22: 22K; R_Axial_DIN0207_L6.3mm_D2.5mm_P10.16mm_Horizontal
RV1, RV4: 100ka; Potentiometer_Omeg_PC16BU_Vertical
RV2: 500Ka; Potentiometer_Omeg_PC16BU_Vertical
RV3: 25KB; Potentiometer_Omeg_PC16BU_Vertical
RV5: 2kB; Potentiometer_Omeg_PC16BU_Vertical
SW1: SW_DPDT_x2; SWITCH-M1-DPDT

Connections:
9v: J1.5, R2.2
GND: C1.2, C3.2, C6.2, C17.2, J1.1, J1.2, R1.2, R5.2, R6.2, R9.1, R11.1, R14.2, R15.1, R17.2, R20.2, R21.1, RV1.1, RV5.1, SW1.2 (B), SW1.5 (B)
IN: J1.3, R1.1, R3.2
unnamed: C2.1, C5.1, R5.1, R23.2, SW1.3 (C), SW1.6 (C)
unnamed: C2.2, R4.1, R12.1
unnamed: C3.1, C4.2, R3.1
unnamed: C4.1, Q1.3 (G), R6.1
unnamed: C5.2, R4.2, R7.1
unnamed: C6.1, Q1.2 (S), R9.2
unnamed: C7.1, R10.2
unnamed: C7.2, Q1.1 (D), R8.1
unnamed: C8.1, Q2.3 (G), Q4.3 (G), RV2.2
unnamed: C8.2, R10.1, RV2.3
unnamed: C9.1, Q3.3 (G), R13.2, R14.1
unnamed: C9.2, RV1.2
unnamed: C10.1, Q5.1 (D), Q6.1 (D), R22.1
unnamed: C10.2, R12.2
unnamed: C11.1, Q2.2 (S), Q4.2 (S), R15.2
unnamed: C11.2, SW1.4 (A)
unnamed: C12.1, C16.2, R18.2
unnamed: C12.2, Q2.1 (D), Q4.1 (D), R16.1
unnamed: C13.1, R19.1
unnamed: C13.2, Q3.2 (S), R17.1
unnamed: C14.1, C15.1, R18.1
unnamed: C14.2, RV5.2
unnamed: C15.2, RV3.1, RV4.1, RV4.2
unnamed: C16.1, RV3.3
unnamed: C17.1, Q5.2 (S), Q6.2 (S), R21.2
unnamed: Q5.3 (G), Q6.3 (G), RV3.2
unnamed: R7.2, RV1.3
unnamed: R11.2, RV2.1
unnamed: R23.1, SW1.1 (A)
unnamed: RV4.3, RV5.3
OUT: J1.4, R19.2, R20.1
VA: C1.1, Q3.1 (D), R2.1, R8.2, R13.1, R16.2, R22.2
